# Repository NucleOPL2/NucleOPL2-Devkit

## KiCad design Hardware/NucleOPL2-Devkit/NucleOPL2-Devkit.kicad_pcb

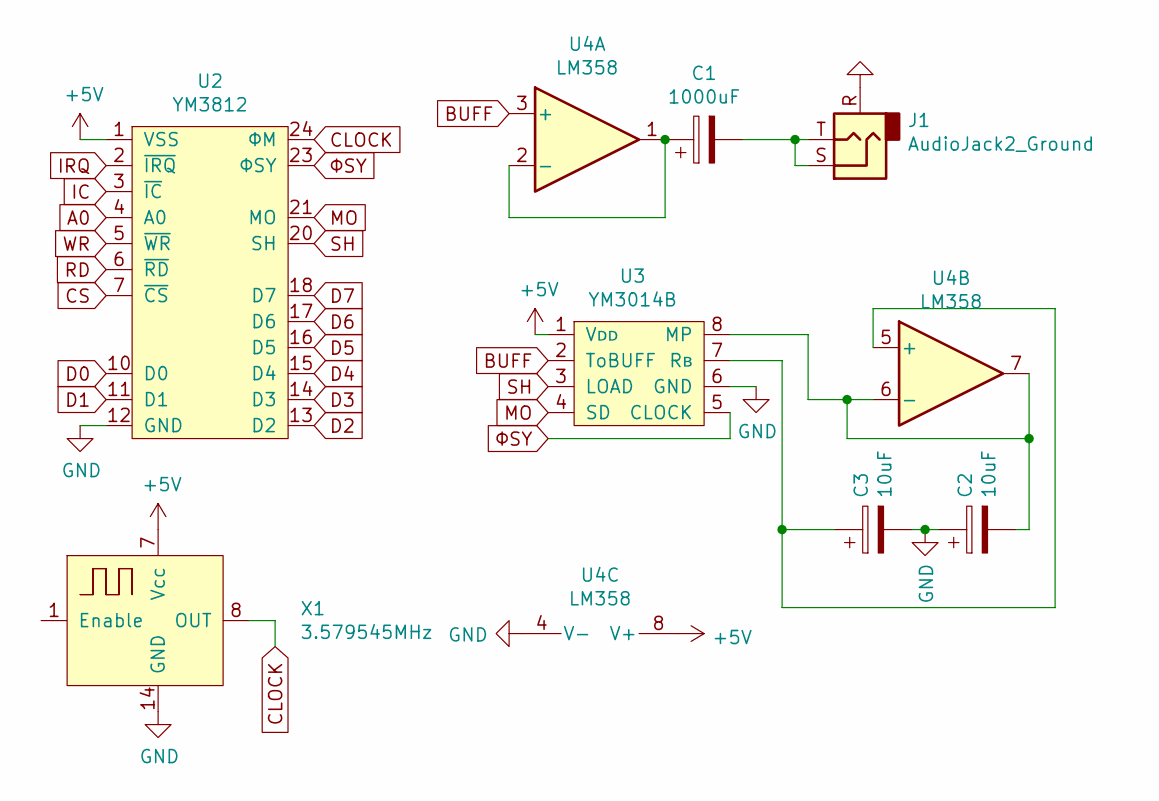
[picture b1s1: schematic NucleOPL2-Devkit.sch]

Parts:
C1: 1000uF; CP_Radial_D8.0mm_P3.50mm
C2, C3: 10uF; CP_Radial_D8.0mm_P3.50mm
J1: AudioJack2_Ground; Jack_3.5mm_CUI_SJ1-3533NG_Horizontal
U2: YM3812; DIP-24_W15.24mm
U3: YM3014B; DIP-8_W7.62mm
U4: LM358; DIP-8_W7.62mm
X1: 3.579545MHz; Oscillator_DIP-14

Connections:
+5V: U2.1 (VSS), U3.1 (Vᴅᴅ), U4.8 (V+), X1.7 (Vcc)
A0: U2.4 (A0)
BUFF: U3.2 (ToBUFF), U4.3 (+)
CLOCK: U2.24 (ΦM), X1.8 (OUT)
CS: U2.7 (~CS)
D0: U2.10 (D0)
D1: U2.11 (D1)
D2: U2.13 (D2)
D3: U2.14 (D3)
D4: U2.15 (D4)
D5: U2.16 (D5)
D6: U2.17 (D6)
D7: U2.18 (D7)
GND: C2.1, C3.2, J1.R, U2.12 (GND), U3.6 (GND), U4.4 (V-), X1.14 (GND)
IC: U2.3 (~IC)
IRQ: U2.2 (~IRQ)
MO: U2.21 (MO), U3.4 (SD)
unnamed: C1.1, U4.1, U4.2 (-)
unnamed: C1.2, J1.S, J1.T
unnamed: C2.2, U3.8 (MP), U4.6 (-), U4.7
unnamed: C3.1, U3.7 (Rʙ), U4.5 (+)
RD: U2.6 (~RD)
SH: U2.20 (SH), U3.3 (LOAD)
WR: U2.5 (~WR)
ΦSY: U2.23 (ΦSY), U3.5 (CLOCK)

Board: 2 copper layers, 9 parts (0 on the bottom side), 11 nets, no tracks yet.

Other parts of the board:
J1#2: 3.5mm_Jack; Jack_3.5mm_Neutrik_NMJ6HCD2_Horizontal

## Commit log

2019-11-10 First commit.
2019-11-10 Ignored files.
    Renamed NucleOPL2.lib -> NucleOPL2-Devkit.lib.
